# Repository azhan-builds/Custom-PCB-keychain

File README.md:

# Custom PCB keychain

A small PCB keychain, custom designed using eleven addressable RGB Leds placed in the shape of an initial('W' here). A button is used to change the animation, and shaking the keychain also changes it.

## What it does

- Uses seven addressable RGB Leds to animate the initial 'W'
- Custom animations on the keychain
- A button to change the animation manually
- Shaking or tiliting also changes the animation
- Cool hidden animations too
- A chargin animation, and the initial shows the battery level too
- Rechargable using usb-c

## Hardware

- ATtiny1614 microcontroller
- SK6812 Mini-e rgb leds x11
- Accelerometer, preferably LIS2DH12
- Li-ion puch cell
- MCP73831 single  cell li-ion charger IC
- MCP1700-3302 regulator 
- TPS61022 boost converter
- SN74AHCT1G125 buffer
- 3 pin UPDI programmer
- USB-c charging port
- tacticle button
- slide switch as power switch
- 100nF and 10uF capacitors for decouplling
- 330ohm resistor
- 402030 li-ion pouch cell.

## Status

hardware has been finalized so far, and the next step is the schematics. The choice of software will be Kicad.

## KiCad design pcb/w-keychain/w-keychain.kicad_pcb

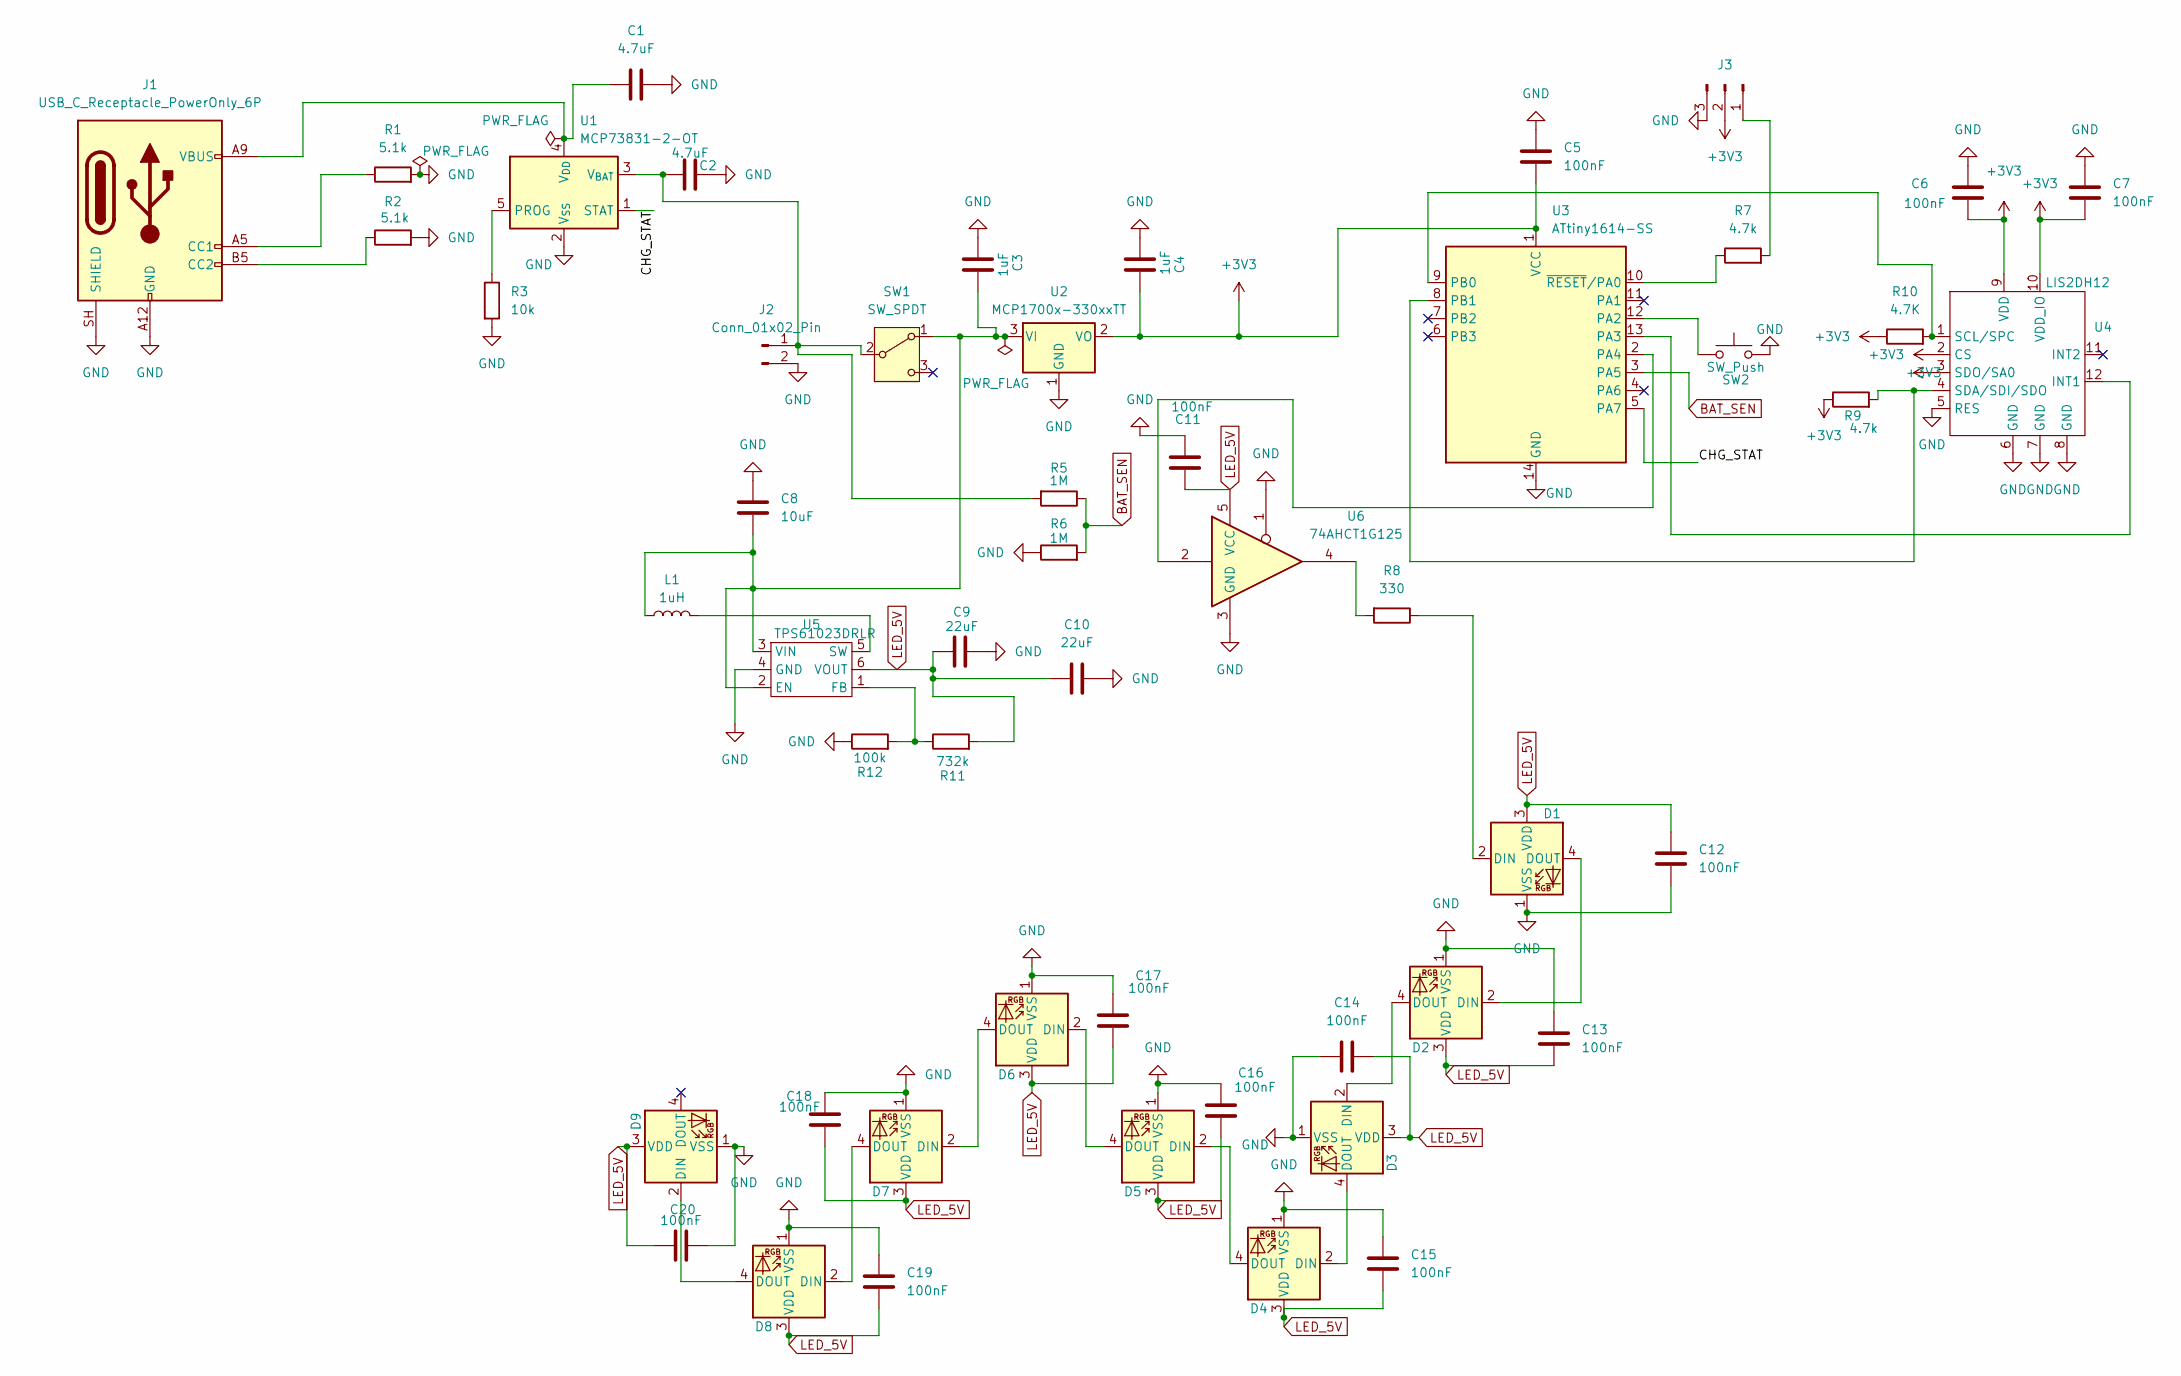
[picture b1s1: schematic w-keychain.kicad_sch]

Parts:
C1, C2: 4.7uF; C_0805_2012Metric
C3, C4: 1uF; C_0603_1608Metric
C5, C6, C7, C11, C12, C13, C14, C15, C16, C17, C18, C19, C20: 100nF; C_0603_1608Metric
C8: 10uF; C_0805_2012Metric
C9, C10: 22uF; C_0805_2012Metric
D1, D2, D3, D4, D5, D6, D7, D8, D9: SK6812MINI-E; LED_SK6812MINI-E_3.2x2.8mm_P1.5mm_ReverseMount
J1: USB_C_Receptacle_PowerOnly_6P; USB_C_Receptacle_GCT_USB4125-xx-x-0190_6P_TopMnt_Horizontal
J2: Conn_01x02_Pin; Battery_Wire_Pads_2x_SMD
J3: Programming pads; UPDI_Pads_1x03_P2.54mm_SMD
L1: 1uH; L_1008_2520Metric
R1, R2: 5.1k; R_0603_1608Metric
R3: 10k; R_0603_1608Metric
R5, R6: 1M; R_0603_1608Metric
R7, R9: 4.7k; R_0603_1608Metric
R8: 330; R_0603_1608Metric
R10: 4.7K; R_0603_1608Metric
R11: 732k; R_0603_1608Metric
R12: 100k; R_0603_1608Metric
SW1: SW_SPDT; Nidec_Copal_CAS-120A
SW2: SW_Push; SW_SPST_PTS810
U1: MCP73831-2-OT; SOT-23-5
U2: MCP1700x-330xxTT; SOT-23
U3: ATtiny1614-SS; SOIC-14_3.9x8.7mm_P1.27mm
U4: LIS2DH12; LGA-12_2x2mm_P0.5mm
U5: TPS61023DRLR; SOT-563
U6: 74AHCT1G125; SOT-23-5

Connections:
+3V3: C4.1, C5.2, C6.2, C7.2, J3.2 (3v3), R9.1, R10.1, U2.2 (VO), U3.1 (VCC), U4.2 (CS), U4.3 (SDO/SA0), U4.9 (VDD), U4.10 (VDD_IO)
/CHG_STAT: U1.1 (STAT), U3.5 (PA7)
BAT_SEN: R5.1, R6.2, U3.3 (PA5)
GND: C1.2, C2.2, C3.2, C4.2, C5.1, C6.1, C7.1, C8.1, C9.2, C10.2, C11.1, C12.2, C13.1, C14.1, C15.1, C16.1, C17.1, C18.1, C19.1, C20.2, D1.1 (VSS), D2.1 (VSS), D3.1 (VSS), D4.1 (VSS), D5.1 (VSS), D6.1 (VSS), D7.1 (VSS), D8.1 (VSS), D9.1 (VSS), J1.A12 (GND), J1.B12 (GND), J1.SH (SHIELD), J2.2, J3.3 (GND), R1.2, R2.2, R3.2, R6.1, R12.1, SW2.2, U1.2 (V_{SS}), U2.1 (GND), U3.14 (GND), U4.5 (RES), U4.6 (GND), U4.7 (GND), U4.8 (GND), U5.4 (GND), U6.1, U6.3 (GND)
LED_5V: C9.1, C10.1, C11.2, C12.1, C13.2, C14.2, C15.2, C16.2, C17.2, C18.2, C19.2, C20.1, D1.3 (VDD), D2.3 (VDD), D3.3 (VDD), D4.3 (VDD), D5.3 (VDD), D6.3 (VDD), D7.3 (VDD), D8.3 (VDD), D9.3 (VDD), R11.2, U5.6 (VOUT), U6.5 (VCC)
unnamed: D1.2 (DIN), R8.1
unnamed: D1.4 (DOUT), D2.2 (DIN)
unnamed: D2.4 (DOUT), D3.2 (DIN)
unnamed: D3.4 (DOUT), D4.2 (DIN)
unnamed: D4.4 (DOUT), D5.2 (DIN)
unnamed: D5.4 (DOUT), D6.2 (DIN)
unnamed: D6.4 (DOUT), D7.2 (DIN)
unnamed: D7.4 (DOUT), D8.2 (DIN)
unnamed: D8.4 (DOUT), D9.2 (DIN)
unnamed: J1.A5 (CC1), R1.1
unnamed: J1.B5 (CC2), R2.1
unnamed: C2.1, J2.1, R5.2, SW1.2 (B), U1.3 (V_{BAT})
unnamed: J3.1 (UPDI), R7.2
unnamed: R8.2, U6.4
unnamed: C3.1, C8.2, L1.1, SW1.1 (A), U2.3 (VI), U5.2 (EN), U5.3 (VIN)
unnamed: R3.1, U1.5 (PROG)
unnamed: C1.1, J1.A9 (VBUS), J1.B9 (VBUS), U1.4 (V_{DD})
unnamed: SW2.1, U3.12 (PA2)
unnamed: U3.13 (PA3), U4.12 (INT1)
unnamed: U3.2 (PA4), U6.2
unnamed: R10.2, U3.9 (PB0), U4.1 (SCL/SPC)
unnamed: R9.2, U3.8 (PB1), U4.4 (SDA/SDI/SDO)
unnamed: R7.1, U3.10 (~RESET/PA0)
unnamed: R11.1, R12.2, U5.1 (FB)
unnamed: L1.2, U5.5 (SW)

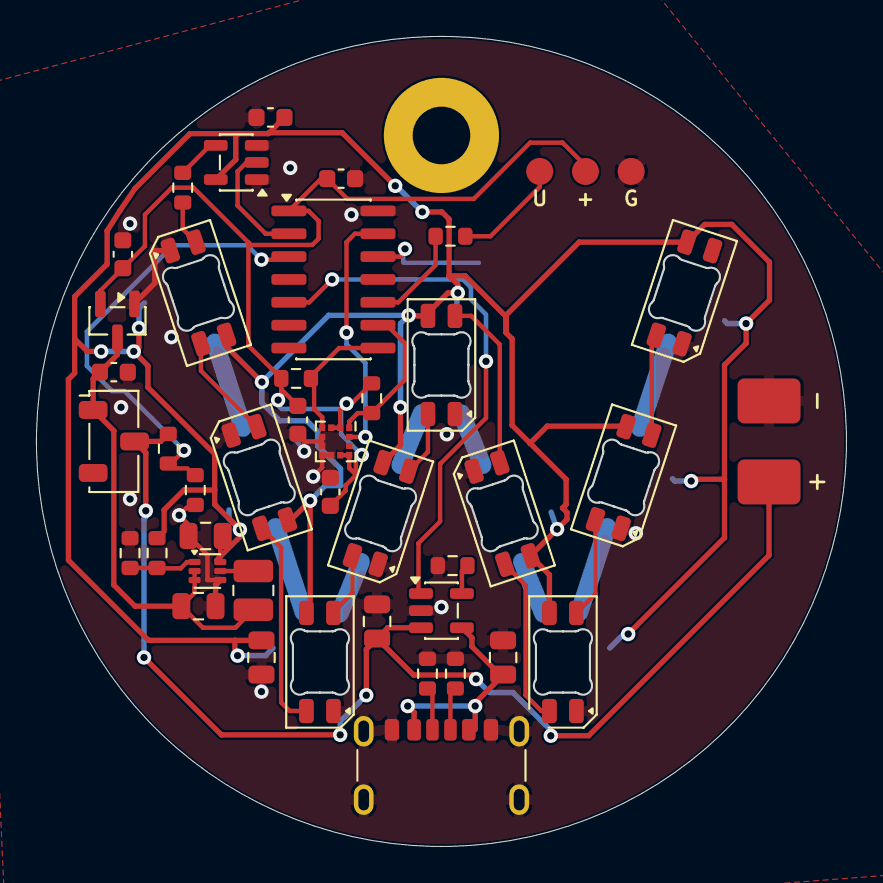
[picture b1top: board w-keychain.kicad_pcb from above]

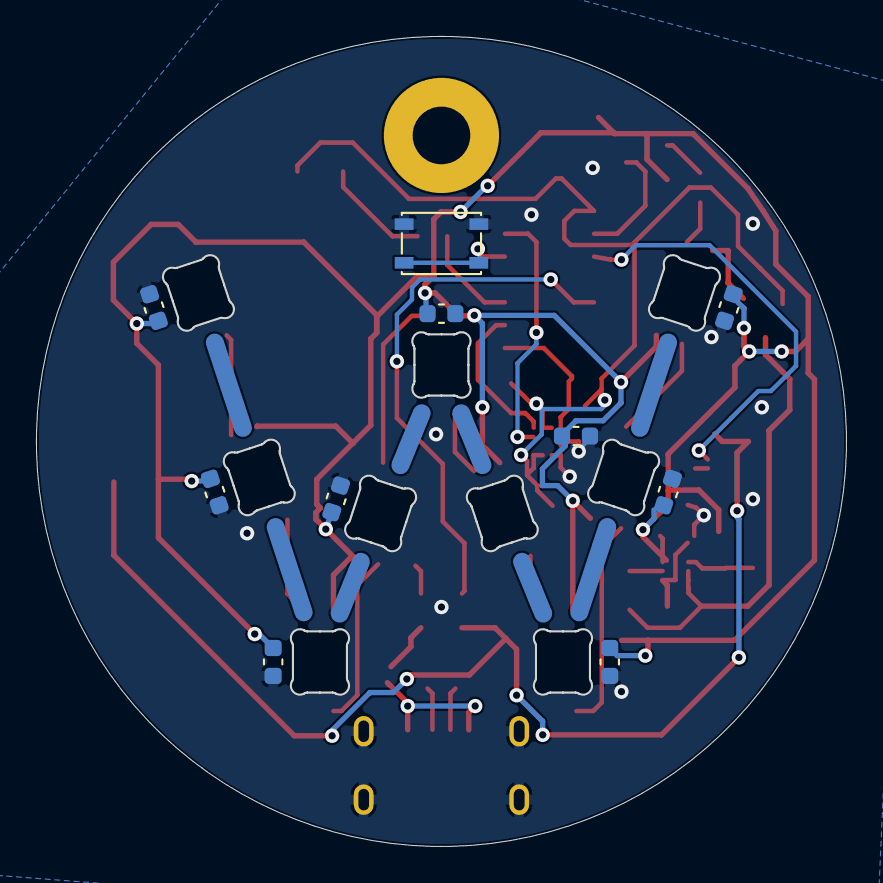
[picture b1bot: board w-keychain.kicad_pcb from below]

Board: 2 copper layers, 45.0 x 45.0 mm, 53 parts (10 on the bottom side), 30 nets.

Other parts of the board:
ART1: W_Gold_Front_Art
